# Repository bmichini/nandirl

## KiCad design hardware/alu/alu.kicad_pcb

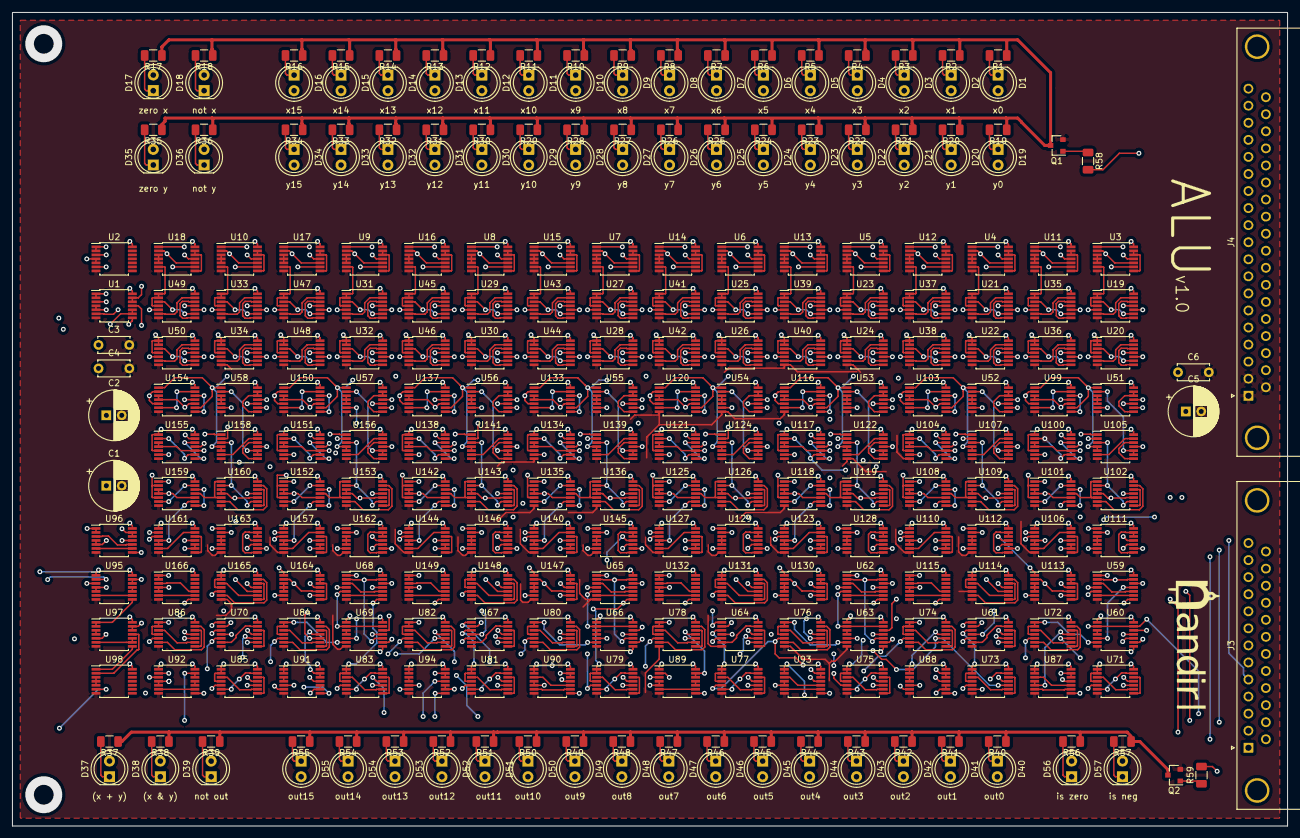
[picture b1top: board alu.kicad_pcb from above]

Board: 4 copper layers, 207.0 x 132.1 mm, 292 parts (0 on the bottom side), 757 nets.

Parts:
C1, C2, C5: 100uF; CP_Radial_D8.0mm_P2.50mm
C3, C4, C6: 100nF; C_Disc_D5.0mm_W2.5mm_P5.00mm
D1, D2, D3, D4, D5, D6, D7, D8, D9, D10, D11, D12, D13, D14, D15, D16, D17, D18, D19, D20, D21, D22, D23, D24, D25, D26, D27, D28, D29, D30, D31, D32, D33, D34, D35, D36, D37, D38, D39, D40, D41, D42, D43, D44, D45, D46, D47, D48, D49, D50, D51, D52, D53, D54, D55, D56, D57: LED; LED_D5.0mm
J3: DB25_Male; DSUB-25_Male_Horizontal_P2.77x2.84mm_EdgePinOffset7.70mm_Ho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
J4: DB37_Male; DSUB-37_Male_Horizontal_P2.77x2.84mm_EdgePinOffset7.70mm_Ho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
Q1, Q2: Q_NPN_Darlington_BEC; SOT-23
R1, R2, R3, R4, R5, R6, R7, R8, R9, R10, R11, R12, R13, R14, R15, R16, R17, R18, R19, R20, R21, R22, R23, R24, R25, R26, R27, R28, R29, R30, R31, R32, R33, R34, R35, R36, R37, R38, R39, R40, R41, R42, R43, R44, R45, R46, R47, R48, R49, R50, R51, R52, R53, R54, R55, R56, R57: 1K; R_1206_3216Metric
R58, R59: 5k; R_1206_3216Metric
U1, U2, U3, U4, U5, U6, U7, U8, U9, U10, U11, U12, U13, U14, U15, U16, U17, U18, U19, U20, U21, U22, U23, U24, U25, U26, U27, U28, U29, U30, U31, U32, U33, U34, U35, U36, U37, U38, U39, U40, U41, U42, U43, U44, U45, U46, U47, U48, U49, U50, U51, U52, U53, U54, U55, U56, U57, U58, U59, U60, U61, U62, U63, U64, U65, U66, U67, U68, U69, U70, U71, U72, U73, U74, U75, U76, U77, U78, U79, U80, U81, U82, U83, U84, U85, U86, U87, U88, U89, U90, U91, U92, U93, U94, U95, U96, U97, U98, U99, U100, U101, U102, U103, U104, U105, U106, U107, U108, U109, U110, U111, U112, U113, U114, U115, U116, U117, U118, U119, U120, U121, U122, U123, U124, U125, U126, U127, U128, U129, U130, U131, U132, U133, U134, U135, U136, U137, U138, U139, U140, U141, U142, U143, U144, U145, U146, U147, U148, U149, U150, U151, U152, U153, U154, U155, U156, U157, U158, U159, U160, U161, U162, U163, U164, U165, U166: SN74ALVC00; TSSOP-14_4.4x5mm_P0.65mm

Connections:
+3V3: C1.1, C2.1, C3.1, C4.1, C5.1, C6.1, J4.3, J4.21, U1.14, U2.14, U3.14, U4.14, U5.14, U6.14, U7.14, U8.14, U9.14, U10.14, U11.14, U12.14, U13.14, U14.14, U15.14, U16.14, U17.14, U18.14, U19.14, U20.14, U21.14, U22.14, U23.14, U24.14, U25.14, U26.14, U27.14, U28.14, U29.14, U30.14, U31.14, U32.14, U33.14, U34.14, U35.14, U36.14, U37.14, U38.14, U39.14, U40.14, U41.14, U42.14, U43.14, U44.14, U45.14, U46.14, U47.14, U48.14, U49.14, U50.14, U51.14, U52.14, U53.14, U54.14, U55.14, U56.14, U57.14, U58.14, U59.14, U60.14, U61.14, U62.14, U63.14, U64.14, U65.14, U66.14, U67.14, U68.14, U69.14, U70.14, U71.14, U72.14, U73.14, U74.14, U75.14, U76.14, U77.14, U78.14, U79.14, U80.14, U81.14, U82.14, U83.14, U84.14, U85.14, U86.14, U87.14, U88.14, U89.14, U90.14, U91.14, U92.14, U93.14, U94.14, U95.14, U96.14, U97.14, U98.14, U99.14, U100.14, U101.14, U102.14, U103.14, U104.14, U105.14, U106.14, U107.14, U108.14, U109.14, U110.14, U111.14, U112.14, U113.14, U114.14, U115.14, U116.14, U117.14, U118.14, U119.14, U120.14, U121.14, U122.14, U123.14, U124.14, U125.14, U126.14, U127.14, U128.14, U129.14, U130.14, U131.14, U132.14, U133.14, U134.14, U135.14, U136.14, U137.14, U138.14, U139.14, U140.14, U141.14, U142.14, U143.14, U144.14, U145.14, U146.14, U147.14, U148.14, U149.14, U150.14, U151.14, U152.14, U153.14, U154.14, U155.14, U156.14, U157.14, U158.14, U159.14, U160.14, U161.14, U162.14, U163.14, U164.14, U165.14, U166.14
/LEDs/coll: Q1.3, R1.1, R2.1, R3.1, R4.1, R5.1, R6.1, R7.1, R8.1, R9.1, R10.1, R11.1, R12.1, R13.1, R14.1, R15.1, R16.1, R17.1, R18.1, R19.1, R20.1, R21.1, R22.1, R23.1, R24.1, R25.1, R26.1, R27.1, R28.1, R29.1, R30.1, R31.1, R32.1, R33.1, R34.1, R35.1, R36.1
/LEDs/coll2: Q2.3, R37.1, R38.1, R39.1, R40.1, R41.1, R42.1, R43.1, R44.1, R45.1, R46.1, R47.1, R48.1, R49.1, R50.1, R51.1, R52.1, R53.1, R54.1, R55.1, R56.1, R57.1
/MuxNotOut/in0: U59.8, U71.1, U71.2, U71.4
/MuxNotOut/in1: U60.6, U72.1, U72.2, U72.4
/MuxNotOut/in2: U61.3, U73.1, U73.2, U73.4
/MuxNotOut/in3: U61.11, U74.1, U74.2, U74.4
/MuxNotOut/in4: U62.8, U75.1, U75.2, U75.4
/MuxNotOut/in5: U63.6, U76.1, U76.2, U76.4
/MuxNotOut/in6: U64.3, U77.1, U77.2, U77.4
/MuxNotOut/in7: U64.11, U78.1, U78.2, U78.4
/MuxNotOut/in8: U65.8, U79.1, U79.2, U79.4
/MuxNotOut/in9: U66.6, U80.1, U80.2, U80.4
/MuxNotOut/in10: U67.3, U81.1, U81.2, U81.4
/MuxNotOut/in11: U67.11, U82.1, U82.2, U82.4
/MuxNotOut/in12: U68.8, U83.1, U83.2, U83.4
/MuxNotOut/in13: U69.6, U84.1, U84.2, U84.4
/MuxNotOut/in14: U70.3, U85.1, U85.2, U85.4
/MuxNotOut/in15: U70.11, U86.1, U86.2, U86.4
/MuxNotX/in0: U3.6, U19.1, U19.2, U19.4
/MuxNotX/in1: U3.11, U20.1, U20.2, U20.4
/MuxNotX/in2: U4.6, U21.1, U21.2, U21.4
/MuxNotX/in3: U4.11, U22.1, U22.2, U22.4
/MuxNotX/in4: U5.6, U23.1, U23.2, U23.4
/MuxNotX/in5: U5.11, U24.1, U24.2, U24.4
/MuxNotX/in6: U6.6, U25.1, U25.2, U25.4
/MuxNotX/in7: U6.11, U26.1, U26.2, U26.4
/MuxNotX/in8: U7.6, U27.1, U27.2, U27.4
/MuxNotX/in9: U7.11, U28.1, U28.2, U28.4
/MuxNotX/in10: U8.6, U29.1, U29.2, U29.4
/MuxNotX/in11: U8.11, U30.1, U30.2, U30.4
/MuxNotX/in12: U9.6, U31.1, U31.2, U31.4
/MuxNotX/in13: U9.11, U32.1, U32.2, U32.4
/MuxNotX/in14: U10.6, U33.1, U33.2, U33.4
/MuxNotX/in15: U10.11, U34.1, U34.2, U34.4
/MuxNotY/in0: U11.6, U35.1, U35.2, U35.4
/MuxNotY/in1: U11.11, U36.1, U36.2, U36.4
/MuxNotY/in2: U12.6, U37.1, U37.2, U37.4
/MuxNotY/in3: U12.11, U38.1, U38.2, U38.4
/MuxNotY/in4: U13.6, U39.1, U39.2, U39.4
/MuxNotY/in5: U13.11, U40.1, U40.2, U40.4
/MuxNotY/in6: U14.6, U41.1, U41.2, U41.4
/MuxNotY/in7: U14.11, U42.1, U42.2, U42.4
/MuxNotY/in8: U15.6, U43.1, U43.2, U43.4
/MuxNotY/in9: U15.11, U44.1, U44.2, U44.4
/MuxNotY/in10: U16.6, U45.1, U45.2, U45.4
/MuxNotY/in11: U16.11, U46.1, U46.2, U46.4
/MuxNotY/in12: U17.6, U47.1, U47.2, U47.4
/MuxNotY/in13: U17.11, U48.1, U48.2, U48.4
/MuxNotY/in14: U18.6, U49.1, U49.2, U49.4
/MuxNotY/in15: U18.11, U50.1, U50.2, U50.4
/TestZero/0or1: U87.8, U93.1, U93.2
/TestZero/0or1or2or3: U93.8, U96.1, U96.2
/TestZero/0to7: U96.8, U97.12, U97.13
/TestZero/2or3: U88.6, U93.4, U93.5
/TestZero/4or5: U89.3, U93.12, U93.13
/TestZero/4or5or6or7: U94.6, U96.4, U96.5
/TestZero/6or7: U89.8, U94.1, U94.2
/TestZero/8or9: U90.8, U94.9, U94.10
/TestZero/8or9or10or11: U95.3, U96.12, U96.13
/TestZero/8to15: U97.6, U97.9, U97.10
/TestZero/10or11: U91.6, U94.12, U94.13
/TestZero/12or13: U92.3, U95.4, U95.5
/TestZero/12or13or14or15: U95.8, U97.1, U97.2
/TestZero/14or15: U92.8, U95.12, U95.13
/X plus Y/Bits0to3/c0: U102.2, U102.9, U105.3
/X plus Y/Bits0to3/c1: U104.2, U104.9, U106.3
/X plus Y/Bits0to3/c2: U107.3, U109.2, U109.9
/X plus Y/Bits0to3/c3: U110.3, U114.10
/X plus Y/Bits0to3/g0: U111.6, U112.9
/X plus Y/Bits0to3/g0p1: U112.11, U113.1
/X plus Y/Bits0to3/g0p1p2p3: U113.6, U115.1, U115.2
/X plus Y/Bits0to3/p0: U105.11, U111.9
/X plus Y/Bits0to3/p0p1: U111.11, U113.9
/X plus Y/Bits0to3/p0p1p2p3: U113.11, U114.1, U114.2, U114.4
/X plus Y/Bits0to3/p1: U106.11, U111.10, U112.10
/X plus Y/Bits0to3/p2: U107.11, U112.1
/X plus Y/Bits0to3/p2p3: U112.6, U113.2, U113.10
/X plus Y/Bits0to3/p3: U110.11, U112.2
/X plus Y/Bits0to3/~p0p1p2p3: U114.3, U114.9
/X plus Y/Bits4to7/c0: U119.2, U119.9, U122.3
/X plus Y/Bits4to7/c1: U121.2, U121.9, U123.3
/X plus Y/Bits4to7/c2: U124.3, U126.2, U126.9
/X plus Y/Bits4to7/c3: U127.3, U131.10
/X plus Y/Bits4to7/c_in: U115.8, U117.2, U117.9, U131.5
/X plus Y/Bits4to7/g0: U128.6, U129.9
/X plus Y/Bits4to7/g0p1: U129.11, U130.1
/X plus Y/Bits4to7/g0p1p2p3: U130.6, U132.1, U132.2
/X plus Y/Bits4to7/p0: U122.11, U128.9
/X plus Y/Bits4to7/p0p1: U128.11, U130.9
/X plus Y/Bits4to7/p0p1p2p3: U130.11, U131.1, U131.2, U131.4
/X plus Y/Bits4to7/p1: U123.11, U128.10, U129.10
/X plus Y/Bits4to7/p2: U124.11, U129.1
/X plus Y/Bits4to7/p2p3: U129.6, U130.2, U130.10
/X plus Y/Bits4to7/p3: U127.11, U129.2
/X plus Y/Bits4to7/~p0p1p2p3: U131.3, U131.9
/X plus Y/Bits8to11/c0: U136.2, U136.9, U139.3
/X plus Y/Bits8to11/c1: U138.2, U138.9, U140.3
/X plus Y/Bits8to11/c2: U141.3, U143.2, U143.9
/X plus Y/Bits8to11/c3: U144.3, U148.10
/X plus Y/Bits8to11/c_in: U132.8, U134.2, U134.9, U148.5
/X plus Y/Bits8to11/g0: U145.6, U146.9
/X plus Y/Bits8to11/g0p1: U146.11, U147.1
/X plus Y/Bits8to11/g0p1p2p3: U147.6, U149.1, U149.2
/X plus Y/Bits8to11/p0: U139.11, U145.9
/X plus Y/Bits8to11/p0p1: U145.11, U147.9
/X plus Y/Bits8to11/p0p1p2p3: U147.11, U148.1, U148.2, U148.4
/X plus Y/Bits8to11/p1: U140.11, U145.10, U146.10
/X plus Y/Bits8to11/p2: U141.11, U146.1
/X plus Y/Bits8to11/p2p3: U146.6, U147.2, U147.10
/X plus Y/Bits8to11/p3: U144.11, U146.2
/X plus Y/Bits8to11/~p0p1p2p3: U148.3, U148.9
/X plus Y/Bits12to15/c0: U153.2, U153.9, U156.3
/X plus Y/Bits12to15/c1: U155.2, U155.9, U157.3
/X plus Y/Bits12to15/c2: U158.3, U160.2, U160.9
/X plus Y/Bits12to15/c3: U161.3, U165.10
/X plus Y/Bits12to15/c_in: U149.8, U151.2, U151.9, U165.5
/X plus Y/Bits12to15/g0: U162.6, U163.9
/X plus Y/Bits12to15/g0p1: U163.11, U164.1
/X plus Y/Bits12to15/g0p1p2p3: U164.6, U166.1, U166.2
/X plus Y/Bits12to15/p0: U156.11, U162.9
/X plus Y/Bits12to15/p0p1: U162.11, U164.9
/X plus Y/Bits12to15/p0p1p2p3: U164.11, U165.1, U165.2, U165.4
/X plus Y/Bits12to15/p1: U157.11, U162.10, U163.10
/X plus Y/Bits12to15/p2: U158.11, U163.1
/X plus Y/Bits12to15/p2p3: U163.6, U164.2, U164.10
/X plus Y/Bits12to15/p3: U161.11, U163.2
/X plus Y/Bits12to15/~p0p1p2p3: U165.3, U165.9
GND: C1.2, C2.2, C3.2, C4.2, C5.2, C6.2, J4.1, J4.2, J4.20, Q1.2, Q2.2, U1.7, U2.7, U3.7, U4.7, U5.7, U6.7, U7.7, U8.7, U9.7, U10.7, U11.7, U12.7, U13.7, U14.7, U15.7, U16.7, U17.7, U18.7, U19.7, U20.7, U21.7, U22.7, U23.7, U24.7, U25.7, U26.7, U27.7, U28.7, U29.7, U30.7, U31.7, U32.7, U33.7, U34.7, U35.7, U36.7, U37.7, U38.7, U39.7, U40.7, U41.7, U42.7, U43.7, U44.7, U45.7, U46.7, U47.7, U48.7, U49.7, U50.7, U51.7, U52.7, U53.7, U54.7, U55.7, U56.7, U57.7, U58.7, U59.7, U60.7, U61.7, U62.7, U63.7, U64.7, U65.7, U66.7, U67.7, U68.7, U69.7, U70.7, U71.7, U72.7, U73.7, U74.7, U75.7, U76.7, U77.7, U78.7, U79.7, U80.7, U81.7, U82.7, U83.7, U84.7, U85.7, U86.7, U87.7, U88.7, U89.7, U90.7, U91.7, U92.7, U93.7, U94.7, U95.7, U96.7, U97.7, U98.7, U99.7, U100.2, U100.7, U100.9, U101.7, U102.7, U103.7, U104.7, U105.7, U106.7, U107.7, U108.7, U109.7, U110.7, U111.7, U112.7, U113.7, U114.5, U114.7, U115.7, U116.7, U117.7, U118.7, U119.7, U120.7, U121.7, U122.7, U123.7, U124.7, U125.7, U126.7, U127.7, U128.7, U129.7, U130.7, U131.7, U132.7, U133.7, U134.7, U135.7, U136.7, U137.7, U138.7, U139.7, U140.7, U141.7, U142.7, U143.7, U144.7, U145.7, U146.7, U147.7, U148.7, U149.7, U150.7, U151.7, U152.7, U153.7, U154.7, U155.7, U156.7, U157.7, U158.7, U159.7, U160.7, U161.7, U162.7, U163.7, U164.7, U165.7, U166.7
unnamed: D1.1, R1.2
unnamed: D2.1, R2.2
unnamed: D3.1, R3.2
unnamed: D4.1, R4.2
unnamed: D5.1, R5.2
unnamed: D6.1, R6.2
unnamed: D7.1, R7.2
unnamed: D8.1, R8.2
unnamed: D9.1, R9.2
unnamed: D10.1, R10.2
unnamed: D11.1, R11.2
unnamed: D12.1, R12.2
unnamed: D13.1, R13.2
unnamed: D14.1, R14.2
unnamed: D15.1, R15.2
unnamed: D16.1, R16.2
unnamed: D17.1, R17.2
unnamed: D18.1, R18.2
unnamed: D19.1, R19.2
unnamed: D20.1, R20.2
unnamed: D21.1, R21.2
unnamed: D22.1, R22.2
unnamed: D23.1, R23.2
unnamed: D24.1, R24.2
unnamed: D25.1, R25.2
unnamed: D26.1, R26.2
unnamed: D27.1, R27.2
unnamed: D28.1, R28.2
unnamed: D29.1, R29.2
unnamed: D30.1, R30.2
unnamed: D31.1, R31.2
unnamed: D32.1, R32.2
unnamed: D33.1, R33.2
unnamed: D34.1, R34.2
unnamed: D35.1, R35.2
unnamed: D36.1, R36.2
unnamed: D37.1, R37.2
unnamed: D38.1, R38.2
unnamed: D39.1, R39.2
unnamed: D40.1, R40.2
unnamed: D41.1, R41.2
unnamed: D42.1, R42.2
unnamed: D43.1, R43.2
unnamed: D44.1, R44.2
unnamed: D45.1, R45.2
unnamed: D46.1, R46.2
unnamed: D47.1, R47.2
unnamed: D48.1, R48.2
unnamed: D49.1, R49.2
unnamed: D50.1, R50.2
unnamed: D51.1, R51.2
unnamed: D52.1, R52.2
unnamed: D53.1, R53.2
unnamed: D54.1, R54.2
unnamed: D55.1, R55.2
unnamed: D56.1, R56.2
unnamed: D57.1, R57.2
unnamed: Q1.1, R58.1
unnamed: Q2.1, R59.1
unnamed: U3.3, U3.4, U3.5
unnamed: U3.8, U3.12, U3.13
unnamed: U4.3, U4.4, U4.5
unnamed: U4.8, U4.12, U4.13
unnamed: U5.3, U5.4, U5.5
unnamed: U5.8, U5.12, U5.13
unnamed: U6.3, U6.4, U6.5
unnamed: U6.8, U6.12, U6.13
unnamed: U7.3, U7.4, U7.5
unnamed: U7.8, U7.12, U7.13
unnamed: U8.3, U8.4, U8.5
unnamed: U8.8, U8.12, U8.13
unnamed: U9.3, U9.4, U9.5
unnamed: U9.8, U9.12, U9.13
unnamed: U10.3, U10.4, U10.5
unnamed: U10.8, U10.12, U10.13
unnamed: U11.3, U11.4, U11.5
unnamed: U11.8, U11.12, U11.13
unnamed: U12.3, U12.4, U12.5
unnamed: U12.8, U12.12, U12.13
unnamed: U13.3, U13.4, U13.5
unnamed: U13.8, U13.12, U13.13
unnamed: U14.3, U14.4, U14.5
unnamed: U14.8, U14.12, U14.13
unnamed: U15.3, U15.4, U15.5
unnamed: U15.8, U15.12, U15.13
unnamed: U16.3, U16.4, U16.5
unnamed: U16.8, U16.12, U16.13
unnamed: U17.3, U17.4, U17.5
unnamed: U17.8, U17.12, U17.13
unnamed: U18.3, U18.4, U18.5
unnamed: U18.8, U18.12, U18.13
unnamed: U19.3, U19.9
unnamed: U19.8, U19.12
unnamed: U19.6, U19.13
unnamed: U20.3, U20.9
unnamed: U20.8, U20.12
unnamed: U20.6, U20.13
unnamed: U21.3, U21.9
unnamed: U21.8, U21.12
unnamed: U21.6, U21.13
unnamed: U22.3, U22.9
unnamed: U22.8, U22.12
unnamed: U22.6, U22.13
unnamed: U23.3, U23.9
unnamed: U23.8, U23.12
unnamed: U23.6, U23.13
unnamed: U24.3, U24.9
unnamed: U24.8, U24.12
unnamed: U24.6, U24.13
unnamed: U25.3, U25.9
unnamed: U25.8, U25.12
unnamed: U25.6, U25.13
unnamed: U26.3, U26.9
unnamed: U26.8, U26.12
unnamed: U26.6, U26.13
unnamed: U27.3, U27.9
unnamed: U27.8, U27.12
unnamed: U27.6, U27.13
unnamed: U28.3, U28.9
unnamed: U28.8, U28.12
unnamed: U28.6, U28.13
unnamed: U29.3, U29.9
unnamed: U29.8, U29.12
unnamed: U29.6, U29.13
unnamed: U30.3, U30.9
unnamed: U30.8, U30.12
unnamed: U30.6, U30.13
unnamed: U31.3, U31.9
unnamed: U31.8, U31.12
unnamed: U31.6, U31.13
unnamed: U32.3, U32.9
unnamed: U32.8, U32.12
unnamed: U32.6, U32.13
unnamed: U33.3, U33.9
unnamed: U33.8, U33.12
unnamed: U33.6, U33.13
unnamed: U34.3, U34.9
unnamed: U34.8, U34.12
unnamed: U34.6, U34.13
unnamed: U35.3, U35.9
unnamed: U35.8, U35.12
unnamed: U35.6, U35.13
unnamed: U36.3, U36.9
unnamed: U36.8, U36.12
unnamed: U36.6, U36.13
unnamed: U37.3, U37.9
unnamed: U37.8, U37.12
unnamed: U37.6, U37.13
unnamed: U38.3, U38.9
unnamed: U38.8, U38.12
unnamed: U38.6, U38.13
unnamed: U39.3, U39.9
unnamed: U39.8, U39.12
unnamed: U39.6, U39.13
unnamed: U40.3, U40.9
unnamed: U40.8, U40.12
unnamed: U40.6, U40.13
unnamed: U41.3, U41.9
unnamed: U41.8, U41.12
unnamed: U41.6, U41.13
unnamed: U42.3, U42.9
unnamed: U42.8, U42.12
unnamed: U42.6, U42.13
unnamed: U43.3, U43.9
unnamed: U43.8, U43.12
unnamed: U43.6, U43.13
unnamed: U44.3, U44.9
unnamed: U44.8, U44.12
unnamed: U44.6, U44.13
unnamed: U45.3, U45.9
unnamed: U45.8, U45.12
unnamed: U45.6, U45.13
unnamed: U46.3, U46.9
unnamed: U46.8, U46.12
unnamed: U46.6, U46.13
unnamed: U47.3, U47.9
unnamed: U47.8, U47.12
unnamed: U47.6, U47.13
unnamed: U48.3, U48.9
unnamed: U48.8, U48.12
unnamed: U48.6, U48.13
unnamed: U49.3, U49.9
unnamed: U49.8, U49.12
unnamed: U49.6, U49.13
unnamed: U50.3, U50.9
unnamed: U50.8, U50.12
unnamed: U50.6, U50.13
unnamed: U51.3, U51.4, U51.5
unnamed: U51.8, U51.12, U51.13
unnamed: U52.3, U52.4, U52.5
unnamed: U52.8, U52.12, U52.13
unnamed: U53.3, U53.4, U53.5
unnamed: U53.8, U53.12, U53.13
unnamed: U54.3, U54.4, U54.5
unnamed: U54.8, U54.12, U54.13
unnamed: U55.3, U55.4, U55.5
unnamed: U55.8, U55.12, U55.13
unnamed: U56.3, U56.4, U56.5
unnamed: U56.8, U56.12, U56.13
unnamed: U57.3, U57.4, U57.5
unnamed: U57.8, U57.12, U57.13
unnamed: U58.3, U58.4, U58.5
unnamed: U58.8, U58.12, U58.13
unnamed: U59.6, U59.9
unnamed: U59.3, U59.10
unnamed: U59.11, U60.5
unnamed: U60.3, U60.4
unnamed: U60.8, U61.1
unnamed: U60.11, U61.2
unnamed: U61.8, U61.12
unnamed: U61.6, U61.13
unnamed: U62.6, U62.9
unnamed: U62.3, U62.10
unnamed: U62.11, U63.5
unnamed: U63.3, U63.4
unnamed: U63.8, U64.1
unnamed: U63.11, U64.2
unnamed: U64.8, U64.12
unnamed: U64.6, U64.13
unnamed: U65.6, U65.9
unnamed: U65.3, U65.10
unnamed: U65.11, U66.5
unnamed: U66.3, U66.4
unnamed: U66.8, U67.1
unnamed: U66.11, U67.2
unnamed: U67.8, U67.12
unnamed: U67.6, U67.13
unnamed: U68.6, U68.9
unnamed: U68.3, U68.10
unnamed: U68.11, U69.5
unnamed: U69.3, U69.4
unnamed: U69.8, U70.1
unnamed: U69.11, U70.2
unnamed: U70.8, U70.12
unnamed: U70.6, U70.13
unnamed: U71.3, U71.9
unnamed: U71.8, U71.12
unnamed: U71.6, U71.13
unnamed: U72.3, U72.9
unnamed: U72.8, U72.12
unnamed: U72.6, U72.13
unnamed: U73.3, U73.9
unnamed: U73.8, U73.12
unnamed: U73.6, U73.13
unnamed: U74.3, U74.9
unnamed: U74.8, U74.12
unnamed: U74.6, U74.13
unnamed: U75.3, U75.9
unnamed: U75.8, U75.12
unnamed: U75.6, U75.13
unnamed: U76.3, U76.9
unnamed: U76.8, U76.12
unnamed: U76.6, U76.13
unnamed: U77.3, U77.9
unnamed: U77.8, U77.12
unnamed: U77.6, U77.13
unnamed: U78.3, U78.9
unnamed: U78.8, U78.12
unnamed: U78.6, U78.13
unnamed: U79.3, U79.9
unnamed: U79.8, U79.12
unnamed: U79.6, U79.13
unnamed: U80.3, U80.9
unnamed: U80.8, U80.12
unnamed: U80.6, U80.13
unnamed: U81.3, U81.9
unnamed: U81.8, U81.12
unnamed: U81.6, U81.13
unnamed: U82.3, U82.9
unnamed: U82.8, U82.12
unnamed: U82.6, U82.13
unnamed: U83.3, U83.9
unnamed: U83.8, U83.12
unnamed: U83.6, U83.13
unnamed: U84.3, U84.9
unnamed: U84.8, U84.12
unnamed: U84.6, U84.13
unnamed: U85.3, U85.9
unnamed: U85.8, U85.12
unnamed: U85.6, U85.13
unnamed: U86.3, U86.9
unnamed: U86.8, U86.12
unnamed: U86.6, U86.13
unnamed: U87.6, U87.9
unnamed: U87.3, U87.10
unnamed: U87.11, U88.5
unnamed: U88.3, U88.4
unnamed: U88.8, U89.1
unnamed: U88.11, U89.2
unnamed: U89.6, U89.9
unnamed: U89.10, U89.11
unnamed: U90.6, U90.9
unnamed: U90.3, U90.10
unnamed: U90.11, U91.5
unnamed: U91.3, U91.4
unnamed: U91.8, U92.1
unnamed: U91.11, U92.2
unnamed: U92.6, U92.9
unnamed: U92.10, U92.11
unnamed: U93.6, U93.9
unnamed: U93.3, U93.10
unnamed: U93.11, U94.5
unnamed: U94.3, U94.4
unnamed: U94.8, U95.1
unnamed: U94.11, U95.2
unnamed: U95.6, U95.9
unnamed: U95.10, U95.11
unnamed: U96.6, U96.9
unnamed: U96.3, U96.10
unnamed: U96.11, U97.5
unnamed: U97.3, U97.4
unnamed: U97.8, U98.1
unnamed: U97.11, U98.2
unnamed: U98.3, U98.4, U98.5
unnamed: U99.8, U99.12
unnamed: U99.6, U99.13
unnamed: U99.11, U100.1, U100.5
unnamed: U100.3, U100.4, U100.10, U105.1
unnamed: U100.8, U100.12
unnamed: U100.6, U100.13
unnamed: U101.3, U101.4, U101.10, U106.2
unnamed: U101.11, U102.1, U102.5
unnamed: U101.8, U101.12
unnamed: U101.6, U101.13
unnamed: U102.3, U102.4, U102.10, U106.1
unnamed: U102.8, U102.12
unnamed: U102.6, U102.13
unnamed: U103.3, U103.4, U103.10, U107.2
unnamed: U103.11, U104.1, U104.5
unnamed: U103.8, U103.12
unnamed: U103.6, U103.13
unnamed: U104.3, U104.4, U104.10, U107.1
unnamed: U104.8, U104.12
unnamed: U104.6, U104.13
unnamed: U99.3, U99.4, U99.10, U105.2
unnamed: U105.8, U105.12
unnamed: U105.6, U105.13
unnamed: U106.8, U106.12
unnamed: U106.6, U106.13
unnamed: U107.8, U107.12
unnamed: U107.6, U107.13
unnamed: U108.3, U108.4, U108.10, U110.2
unnamed: U108.11, U109.1, U109.5
unnamed: U108.8, U108.12
unnamed: U108.6, U108.13
unnamed: U109.3, U109.4, U109.10, U110.1
unnamed: U109.8, U109.12
unnamed: U109.6, U109.13
unnamed: U110.8, U110.12
unnamed: U110.6, U110.13
unnamed: U111.3, U111.4, U111.5
unnamed: U111.8, U111.12, U111.13
unnamed: U112.3, U112.4, U112.5
unnamed: U112.8, U112.12, U112.13
unnamed: U113.3, U113.4, U113.5
unnamed: U113.8, U113.12, U113.13
unnamed: U114.11, U115.4, U115.5
unnamed: U114.8, U114.12
unnamed: U114.6, U114.13
unnamed: U115.6, U115.9
unnamed: U115.3, U115.10
unnamed: U116.3, U116.4, U116.10, U122.2
unnamed: U116.11, U117.1, U117.5
unnamed: U116.8, U116.12
unnamed: U116.6, U116.13
unnamed: U117.3, U117.4, U117.10, U122.1
unnamed: U117.8, U117.12
unnamed: U117.6, U117.13
unnamed: U118.3, U118.4, U118.10, U123.2
unnamed: U118.11, U119.1, U119.5
unnamed: U118.8, U118.12
unnamed: U118.6, U118.13
unnamed: U119.3, U119.4, U119.10, U123.1
unnamed: U119.8, U119.12
unnamed: U119.6, U119.13
unnamed: U120.3, U120.4, U120.10, U124.2
unnamed: U120.11, U121.1, U121.5
unnamed: U120.8, U120.12
unnamed: U120.6, U120.13
unnamed: U121.3, U121.4, U121.10, U124.1
unnamed: U121.8, U121.12
unnamed: U121.6, U121.13
unnamed: U122.8, U122.12
unnamed: U122.6, U122.13
unnamed: U123.8, U123.12
unnamed: U123.6, U123.13
unnamed: U124.8, U124.12
unnamed: U124.6, U124.13
unnamed: U125.3, U125.4, U125.10, U127.2
unnamed: U125.11, U126.1, U126.5
unnamed: U125.8, U125.12
unnamed: U125.6, U125.13
unnamed: U126.3, U126.4, U126.10, U127.1
unnamed: U126.8, U126.12
unnamed: U126.6, U126.13
unnamed: U127.8, U127.12
unnamed: U127.6, U127.13
unnamed: U128.3, U128.4, U128.5
unnamed: U128.8, U128.12, U128.13
unnamed: U129.3, U129.4, U129.5
unnamed: U129.8, U129.12, U129.13
unnamed: U130.3, U130.4, U130.5
unnamed: U130.8, U130.12, U130.13
unnamed: U131.11, U132.4, U132.5
unnamed: U131.8, U131.12
unnamed: U131.6, U131.13
unnamed: U132.6, U132.9
unnamed: U132.3, U132.10
unnamed: U133.3, U133.4, U133.10, U139.2
unnamed: U133.11, U134.1, U134.5
unnamed: U133.8, U133.12
unnamed: U133.6, U133.13
unnamed: U134.3, U134.4, U134.10, U139.1
unnamed: U134.8, U134.12
unnamed: U134.6, U134.13
unnamed: U135.3, U135.4, U135.10, U140.2
unnamed: U135.11, U136.1, U136.5
unnamed: U135.8, U135.12
unnamed: U135.6, U135.13
unnamed: U136.3, U136.4, U136.10, U140.1
unnamed: U136.8, U136.12
unnamed: U136.6, U136.13
unnamed: U137.3, U137.4, U137.10, U141.2
unnamed: U137.11, U138.1, U138.5
unnamed: U137.8, U137.12
unnamed: U137.6, U137.13
unnamed: U138.3, U138.4, U138.10, U141.1
unnamed: U138.8, U138.12
unnamed: U138.6, U138.13
unnamed: U139.8, U139.12
unnamed: U139.6, U139.13
unnamed: U140.8, U140.12
unnamed: U140.6, U140.13
unnamed: U141.8, U141.12
unnamed: U141.6, U141.13
unnamed: U142.3, U142.4, U142.10, U144.2
unnamed: U142.11, U143.1, U143.5
unnamed: U142.8, U142.12
unnamed: U142.6, U142.13
unnamed: U143.3, U143.4, U143.10, U144.1
unnamed: U143.8, U143.12
unnamed: U143.6, U143.13
unnamed: U144.8, U144.12
unnamed: U144.6, U144.13
unnamed: U145.3, U145.4, U145.5
unnamed: U145.8, U145.12, U145.13
unnamed: U146.3, U146.4, U146.5
unnamed: U146.8, U146.12, U146.13
unnamed: U147.3, U147.4, U147.5
unnamed: U147.8, U147.12, U147.13
unnamed: U148.11, U149.4, U149.5
unnamed: U148.8, U148.12
unnamed: U148.6, U148.13
unnamed: U149.6, U149.9
unnamed: U149.3, U149.10
unnamed: U150.3, U150.4, U150.10, U156.2
unnamed: U150.11, U151.1, U151.5
unnamed: U150.8, U150.12
unnamed: U150.6, U150.13
unnamed: U151.3, U151.4, U151.10, U156.1
unnamed: U151.8, U151.12
unnamed: U151.6, U151.13
unnamed: U152.3, U152.4, U152.10, U157.2
unnamed: U152.11, U153.1, U153.5
unnamed: U152.8, U152.12
unnamed: U152.6, U152.13
unnamed: U153.3, U153.4, U153.10, U157.1
unnamed: U153.8, U153.12
unnamed: U153.6, U153.13
unnamed: U154.3, U154.4, U154.10, U158.2
unnamed: U154.11, U155.1, U155.5
unnamed: U154.8, U154.12
unnamed: U154.6, U154.13
unnamed: U155.3, U155.4, U155.10, U158.1
unnamed: U155.8, U155.12
unnamed: U155.6, U155.13
unnamed: U156.8, U156.12
unnamed: U156.6, U156.13
unnamed: U157.8, U157.12
unnamed: U157.6, U157.13
unnamed: U158.8, U158.12
unnamed: U158.6, U158.13
unnamed: U159.3, U159.4, U159.10, U161.2
unnamed: U159.11, U160.1, U160.5
unnamed: U159.8, U159.12
unnamed: U159.6, U159.13
unnamed: U160.3, U160.4, U160.10, U161.1
unnamed: U160.8, U160.12
unnamed: U160.6, U160.13
unnamed: U161.8, U161.12
unnamed: U161.6, U161.13
unnamed: U162.3, U162.4, U162.5
unnamed: U162.8, U162.12, U162.13
unnamed: U163.3, U163.4, U163.5
unnamed: U163.8, U163.12, U163.13
unnamed: U164.3, U164.4, U164.5
unnamed: U164.8, U164.12, U164.13
unnamed: U165.11, U166.4, U166.5
unnamed: U165.8, U165.12
unnamed: U165.6, U165.13
unnamed: U166.6, U166.9
unnamed: U166.3, U166.10
f: D37.2, J3.3, U1.9, U1.10, U59.5, U60.2, U60.13, U61.10, U62.5, U63.2, U63.13, U64.10, U65.5, U66.2, U66.13, U67.10, U68.5, U69.2, U69.13, U70.10
inst_15: J3.5, R58.2, R59.2
no: D39.2, J3.16, U1.12, U1.13, U71.10, U72.10, U73.10, U74.10, U75.10, U76.10, U77.10, U78.10, U79.10, U80.10, U81.10, U82.10, U83.10, U84.10, U85.10, U86.10
notzero_x0: U19.11, U51.1, U99.1, U99.9, U105.4, U105.5, U111.1
notzero_x1: U20.11, U51.9, U101.1, U101.9, U106.4, U106.5
notzero_x2: U21.11, U52.1, U103.1, U103.9, U107.4, U107.5
notzero_x3: U22.11, U52.9, U108.1, U108.9, U110.4, U110.5
notzero_x4: U23.11, U53.1, U116.1, U116.9, U122.4, U122.5, U128.1
notzero_x5: U24.11, U53.9, U118.1, U118.9, U123.4, U123.5
notzero_x6: U25.11, U54.1, U120.1, U120.9, U124.4, U124.5
notzero_x7: U26.11, U54.9, U125.1, U125.9, U127.4, U127.5
notzero_x8: U27.11, U55.1, U133.1, U133.9, U139.4, U139.5, U145.1
notzero_x9: U28.11, U55.9, U135.1, U135.9, U140.4, U140.5
notzero_x10: U29.11, U56.1, U137.1, U137.9, U141.4, U141.5
notzero_x11: U30.11, U56.9, U142.1, U142.9, U144.4, U144.5
notzero_x12: U31.11, U57.1, U150.1, U150.9, U156.4, U156.5, U162.1
notzero_x13: U32.11, U57.9, U152.1, U152.9, U157.4, U157.5
notzero_x14: U33.11, U58.1, U154.1, U154.9, U158.4, U158.5
notzero_x15: U34.11, U58.9, U159.1, U159.9, U161.4, U161.5
notzero_y0: U35.11, U51.2, U99.2, U99.5, U105.9, U105.10, U111.2
notzero_y1: U36.11, U51.10, U101.2, U101.5, U106.9, U106.10
notzero_y2: U37.11, U52.2, U103.2, U103.5, U107.9, U107.10
notzero_y3: U38.11, U52.10, U108.2, U108.5, U110.9, U110.10
notzero_y4: U39.11, U53.2, U116.2, U116.5, U122.9, U122.10, U128.2
notzero_y5: U40.11, U53.10, U118.2, U118.5, U123.9, U123.10
notzero_y6: U41.11, U54.2, U120.2, U120.5, U124.9, U124.10
notzero_y7: U42.11, U54.10, U125.2, U125.5, U127.9, U127.10
notzero_y8: U43.11, U55.2, U133.2, U133.5, U139.9, U139.10, U145.2
notzero_y9: U44.11, U55.10, U135.2, U135.5, U140.9, U140.10
notzero_y10: U45.11, U56.2, U137.2, U137.5, U141.9, U141.10
notzero_y11: U46.11, U56.10, U142.2, U142.5, U144.9, U144.10
notzero_y12: U47.11, U57.2, U150.2, U150.5, U156.9, U156.10, U162.2
notzero_y13: U48.11, U57.10, U152.2, U152.5, U157.9, U157.10
notzero_y14: U49.11, U58.2, U154.2, U154.5, U158.9, U158.10
notzero_y15: U50.11, U58.10, U159.2, U159.5, U161.9, U161.10
nx: D18.2, J3.14, U1.1, U1.2, U19.10, U20.10, U21.10, U22.10, U23.10, U24.10, U25.10, U26.10, U27.10, U28.10, U29.10, U30.10, U31.10, U32.10, U33.10, U34.10
ny: D36.2, J3.15, U1.4, U1.5, U35.10, U36.10, U37.10, U38.10, U39.10, U40.10, U41.10, U42.10, U43.10, U44.10, U45.10, U46.10, U47.10, U48.10, U49.10, U50.10
out0: D40.2, J3.18, U71.11, U87.1, U87.2
out1: D41.2, J3.6, U72.11, U87.4, U87.5
out2: D42.2, J3.19, U73.11, U87.12, U87.13
out3: D43.2, J3.7, U74.11, U88.1, U88.2
out4: D44.2, J3.20, U75.11, U88.9, U88.10
out5: D45.2, J3.8, U76.11, U88.12, U88.13
out6: D46.2, J3.21, U77.11, U89.4, U89.5
out7: D47.2, J3.9, U78.11, U89.12, U89.13
out8: D48.2, J3.22, U79.11, U90.1, U90.2
out9: D49.2, J3.10, U80.11, U90.4, U90.5
out10: D50.2, J3.23, U81.11, U90.12, U90.13
out11: D51.2, J3.11, U82.11, U91.1, U91.2
out12: D52.2, J3.24, U83.11, U91.9, U91.10
out13: D53.2, J3.12, U84.11, U91.12, U91.13
out14: D54.2, J3.25, U85.11, U92.4, U92.5
out15: D55.2, D57.2, J3.4, J3.13, U86.11, U92.12, U92.13
out_zero: D56.2, J3.17, U98.6
x0: D1.2, J4.19, U3.1
x1: D2.2, J4.37, U3.9
x2: D3.2, J4.18, U4.1
x3: D4.2, J4.36, U4.9
x4: D5.2, J4.17, U5.1
x5: D6.2, J4.35, U5.9
x6: D7.2, J4.16, U6.1
x7: D8.2, J4.34, U6.9
x8: D9.2, J4.15, U7.1
x9: D10.2, J4.33, U7.9
x10: D11.2, J4.14, U8.1
x11: D12.2, J4.32, U8.9
x12: D13.2, J4.13, U9.1
x13: D14.2, J4.31, U9.9
x14: D15.2, J4.12, U10.1
x15: D16.2, J4.30, U10.9
xandy_0: U51.6, U59.1
xandy_1: U51.11, U59.12
xandy_2: U52.6, U60.9
xandy_3: U52.11, U61.4
xandy_4: U53.6, U62.1
xandy_5: U53.11, U62.12
xandy_6: U54.6, U63.9
xandy_7: U54.11, U64.4
xandy_8: U55.6, U65.1
xandy_9: U55.11, U65.12
xandy_10: U56.6, U66.9
xandy_11: U56.11, U67.4
xandy_12: U57.6, U68.1
xandy_13: U57.11, U68.12
xandy_14: U58.6, U69.9
xandy_15: U58.11, U70.4
xplusy_0: U59.4, U100.11
xplusy_1: U60.1, U102.11
xplusy_2: U60.12, U104.11
xplusy_3: U61.9, U109.11
xplusy_4: U62.4, U117.11
xplusy_5: U63.1, U119.11
xplusy_6: U63.12, U121.11
xplusy_7: U64.9, U126.11
xplusy_8: U65.4, U134.11
xplusy_9: U66.1, U136.11
xplusy_10: U66.12, U138.11
xplusy_11: U67.9, U143.11
xplusy_12: U68.4, U151.11
xplusy_13: U69.1, U153.11
xplusy_14: U69.12, U155.11
xplusy_15: U70.9, U160.11
y0: D19.2, J4.11, U11.1
y1: D20.2, J4.29, U11.9
y2: D21.2, J4.10, U12.1
y3: D22.2, J4.28, U12.9
y4: D23.2, J4.9, U13.1
y5: D24.2, J4.27, U13.9
y6: D25.2, J4.8, U14.1
y7: D26.2, J4.26, U14.9
y8: D27.2, J4.7, U15.1
y9: D28.2, J4.25, U15.9
y10: D29.2, J4.6, U16.1
y11: D30.2, J4.24, U16.9
y12: D31.2, J4.5, U17.1
y13: D32.2, J4.23, U17.9
y14: D33.2, J4.4, U18.1
y15: D34.2, J4.22, U18.9
zx: D17.2, J3.1, U2.1, U2.2
zy: D35.2, J3.2, U2.4, U2.5
~f: D38.2, U1.8, U59.2, U59.13, U60.10, U61.5, U62.2, U62.13, U63.10, U64.5, U65.2, U65.13, U66.10, U67.5, U68.2, U68.13, U69.10, U70.5
~no: U1.11, U71.5, U72.5, U73.5, U74.5, U75.5, U76.5, U77.5, U78.5, U79.5, U80.5, U81.5, U82.5, U83.5, U84.5, U85.5, U86.5
~nx: U1.3, U19.5, U20.5, U21.5, U22.5, U23.5, U24.5, U25.5, U26.5, U27.5, U28.5, U29.5, U30.5, U31.5, U32.5, U33.5, U34.5
~ny: U1.6, U35.5, U36.5, U37.5, U38.5, U39.5, U40.5, U41.5, U42.5, U43.5, U44.5, U45.5, U46.5, U47.5, U48.5, U49.5, U50.5
~zx: U2.3, U3.2, U3.10, U4.2, U4.10, U5.2, U5.10, U6.2, U6.10, U7.2, U7.10, U8.2, U8.10, U9.2, U9.10, U10.2, U10.10
~zy: U2.6, U11.2, U11.10, U12.2, U12.10, U13.2, U13.10, U14.2, U14.10, U15.2, U15.10, U16.2, U16.10, U17.2, U17.10, U18.2, U18.10
